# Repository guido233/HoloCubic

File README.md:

> 本 Fork 的固件已迁移到 Arduino-ESP32 3.3.12 和 LVGL 9.6，保留原版硬件接口。
> 编译、烧录、板型选择和资源迁移请阅读 [固件维护说明](2.Firmware/HoloCubic-fw/README.md)。
> 下文硬件设计与价格描述保留原作者历史记录；MPU6050 已停产，ESP32-PICO-D4 已标记为 NRND。
> Naive 硬件修订源文件在 [RevB KiCad 工程](1.Hardware/RevB-KiCad/Naive/README.md)。这是待样机验证的工程修订，采购、装配限制及检查命令均写在该目录。

# HoloCubic--多功能透明显示屏桌面站

**视频介绍：** https://www.bilibili.com/video/BV1VA411p7MD/

## 0. 关于本项目

> 稚晖君注：这是为了更新视频，缓解本人拖更两个月的尴尬，用一个周末时间赶出来的一个有意思的小玩意 :D

如视频所述，本项目有意思的地方在于使用了一个分光棱镜来设计出`伪全息显示`的效果。这个小设备总的来说功能比较多，因为搭载了WiFi和蓝牙能力可以实现很多网络应用，在本仓库中给大家提供了一个开发框架以及一些基础功能（天气、粉丝数监视器等），大家可以基于我的方案继续扩展实现更多应用。

本项目的硬件方案是基于`ESP32PICO-D4`的，乐鑫的一个很实用的MCU芯片，由于采用了SiP封装是的PCBA整板面积能做到一个硬币大小；软件方面主要是基于`lvgl-GUI`库，我移植了ST7789 1.3寸`240x240`分辨率屏幕的显示屏驱动，同时将`MPU6050`作为输入设备通过感应的方式模拟编码器键值来交互。

## 1. 硬件打样说明

原 Altium 文件保留作为历史基线。复刻前请先阅读 [Naive RevB 说明](1.Hardware/RevB-KiCad/Naive/README.md)：原板的 USB-C CC、电源、MPU6050 焊盘、上拉与背光驱动存在需要修正或验证的项目。原文的价格是历史估算，不能作为当前采购预算。

`Hardware`文件内目前包含两个版本的PCB电路：

* **Naive Version** ：即视频中出现的版本，板载ESP32、IMU、环境光传感器、SD卡槽、下载电路、以及一颗RGB灯
* **Ironman Version** ：基于上面的版本轻微修改，删去了环境光传感器，修改了PCB形状以适配新的外壳

> 因为新款的外壳计划是使用CNC进行金属加工，因此环境光容易被遮挡，而且该功能使用场景不多所以在新版删去了。

**外壳加工** 根据自己喜欢的版本选择，`3D Model`文件夹目前包含四个版本的外壳文件：

* **Naive Version** ：即视频中出现的版本，比较简约（因为临时赶工设计的），最好使用光固化3D打印加工

* **Bilibili Version** ：视频中后面出现的B站百大奖杯形式的外壳结构，适配`Naive Version`的PCB， **属于娱乐性质，非百大UP不建议采用**。

* **Metal Version** ：视频发布后全新改版的外壳结构设计，优化了布局控件整体更紧凑精致，适配`Naive Version`的PCB，该建议使用CNC加工制作

* **Ironman Version** ：新设计的野生钢铁侠风格结构件，该版本为和朋友合作设计的，后面可能会授权他联名量产，该结构适配`Ironman Version`的PCB

> 野生钢铁侠联名的版本的结构件加工比较复杂，而且需要后期喷砂、阳极氧化等工艺所以单件制造成本很高（打听了下整套3个部件至少要1000元+），因此大家自己有加工渠道的可以用提供的文件自己去做。
>
> 没有渠道但是又想要这个版本硬件的，**我授权了那位朋友量产一小批**，他的店铺名为[Xikii](https://shop68240117.taobao.com)，是做客制化键盘很有经验的一个极客，大家感兴趣的可以去关注一下~

## 2. 固件编译说明

维护版使用 PlatformIO，固定依赖版本，支持 `naive` 和 `ironman` 两种环境。Naive 为一颗 RGB 灯，Ironman 为两颗；以实际 PCB 为准。

```sh
python3 -m venv .venv
. .venv/bin/activate
python -m pip install platformio==6.1.18
pio run -d 2.Firmware/HoloCubic-fw -e naive
```

使用 Python 3.11 或更新版本。Ironman 将最后的环境名替换为 `ironman`。本版不需要复制 `Libraries`，不需要修改 ESP32 SDK 或 TFT_eSPI；屏幕和 SD 引脚由项目配置。新固件使用 4MB Flash 上的 3MiB 应用分区，首次升级应使用完整 PlatformIO 烧录流程。

完整命令、WiFi 配置、依赖版本、迁移事项和验证范围见 [固件维护说明](2.Firmware/HoloCubic-fw/README.md)。默认显示内置 Logo，提供传感器输入、SD 图片与联网查询基础功能，原视频中的所有应用仍需单独实现或移植。

## 3. 模拟器与图片转换

原 `3.Software/LvglSimulator` 的 Visual Studio 工程和 `HoloTool.exe` 保留作历史参考，使用旧版 LVGL，与当前固件的图片和接口格式不同。维护版通过主机 GUI 回归测试检查 LVGL 9 渲染与输入行为。

新版图片转换器支持 Windows、macOS 和 Linux，要求 Python 3.11 或更新版本：

```sh
python -m pip install -r 3.Software/ImageToHolo/requirements.txt
python 3.Software/ImageToHolo/get_holo.py picture.png
```

默认输出原图旁的 `picture.lv9.bin`，是 LVGL 9 RGB565 格式；复制到 SD 后用 `S:/picture.lv9.bin` 访问。原版图片需要从原图重新生成，供旧固件使用时可加 `--legacy-v7` 输出 `picture.lv7.bin`。更多选项见 `--help`。

## 4. 关于分光棱镜

我用的时25.4mm x 25.4mm x 25.4mm的棱镜，淘宝应该可以搜到，单个价格80元左右。

分光棱镜的固定比较麻烦，用胶水的话容易渗入屏幕导致水印，因此建议去TB搜一下`OCA胶`，这是一种`全贴合屏幕工艺`中用来粘合屏幕的固态胶，效果很不错也很便宜。

> 但是OCA粘性非常强，大家操作一定要仔细不要留气泡，不然粘上后就很难取下了。

## 其他的后续再补充，有用的话记得点星星~

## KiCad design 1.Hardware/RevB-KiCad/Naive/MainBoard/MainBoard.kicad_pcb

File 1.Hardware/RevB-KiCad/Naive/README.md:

# HoloCubic Naive RevB 工程修订

本目录维护 Naive 外形的原生 KiCad 10 工程。原作者的 Altium 工程保留在 `1.Hardware/Naive Version/`，没有覆盖。Ironman 尚未作本轮硬件修订。

单台整机材料见 [采购说明](PURCHASING.md)；板上用量见 [BOM.csv](BOM.csv) 和 [合并采购表](BOM-grouped.csv)。

2026-10-30 已应用首台样机的四处物料替代：主板 C24 与显示板 C4 共用 **GRM188R71E105KA12D / C86020**，每台合计 2 颗；主板 U6 改为 **TPS22918DBVT**，主板 R3 改为 **RTT022000FTH / C102869**。两板仍为 69 个位号，合并后为 38 个完整 MPN 采购行。**主板 C4 继续使用 22µF / 0805**，不属于这次 1µF 合并。替代保持原电气网络、焊盘和接口，不要求修改固件；选型已应用不代表已经实测或获得量产放行。

**当前为工程验证版本，尚未完成实物装配和通电验收。** 原生 ERC、DRC、网表一致性检查通过只能证明文件内的相应约束成立；屏幕尾排折弯、外壳净高、天线性能、USB 热插拔与供电波形仍需样机验证。不要根据文件名或一张渲染图直接批量下单。

## 打开工程

使用 KiCad 10.0 或更新的兼容版本，分别打开：

- `MainBoard/MainBoard.kicad_pro`：主板、电源、USB、ESP32、传感器、SD。
- `ExtendBoard/ExtendBoard.kicad_pro`：显示板、FFC、屏幕、背光恒流驱动。

每块板附有本地 `.pretty` 封装库、`.kicad_sym` 符号库和库表，电路与焊盘均在原生文件中，工程并非仅包含一份修改建议。macOS 从完整 KiCad 套件启动原理图编辑器；不要把内部的 `eeschema.app` 单独拷出安装，否则其相对路径共享库可能失效。

## 本轮电路修订

| 部位 | 修订内容与目的 |
| --- | --- |
| USB-C | CC1、CC2 各自接独立 5.1kΩ Rd；数据、CC 与 VBUS 增加所选器件的保护路径。USB 数据线保持两种插头方向的连接关系。 |
| 3.3V 电源 | 原 250mA LP2992 改为 TPS62162 1A 降压方案；增加电感、有效容量设计所需的输入输出电容。TPS22918 控制系统 5V 的上电斜率；RC/CT 时序需要示波器验证。 |
| USB-UART | CP2102 的 VDD6 接独立 `CP_VDD` 本地旁路，不与主板 3.3V 稳压输出并联；REGIN 增加本地去耦。 |
| MPU6050 | 删除原中心焊盘、中心锡膏与孔；中心区域禁止顶层铜、走线和过孔，遵循该封装的装配要求。 |
| ESP32-PICO | 热焊盘使用 4.5mm 接地铜、4.0mm 阻焊开口、21 个 0.25mm 热过孔，以及 16 个 0.75mm 锡膏窗口；与 MPU 的中心禁焊区分别处理。 |
| 总线与启动 | 增加 I²C 外部上拉和 SD DAT1/DAT2 上拉；保留 GPIO12 隔离；EN 电容改为 1µF；BH1750 DVI 增加复位延迟 RC。 |
| RGB | 5V WS2812B 前增加 AHCT 缓冲、旁路、串联电阻及复位默认电平，避免依赖 3.3V 直接驱动 5V 数据输入。 |
| 显示板 | 增加逻辑与 5V 本地去耦；AL5802 加 27Ω 电流设定电阻，背光典型约 24mA；NMOS 分流 EN，保持 GPIO5 低电平点亮的固件极性。 |
| FFC | 两板使用确切的 Hirose FH12-8S-0.5SH(55)，按官方 8 针焊盘替换未识别的旧封装；原文件嵌入的 16 针模型不能用于认证 8 针连接器。 |

主板仍使用 ESP32-PICO-D4、MPU6050、BH1750、CP2102 以维持复刻电路与固件接口。ESP32-PICO 系列已列为 NRND；MPU6050 已停产。它们不是当前可随意等效采购的新设计器件。采购替代、旧料来源及接口验收条件请见 [BOM 审查](BOM-review.md)。

USB1、J1、A1 已分别选定 GCT USB4105-GF-A、Molex 104031-0811、CrossAir CA-C03，采用相应厂图重新定义焊盘。Molex 完全插入后的卡端比原版左移 0.65mm，以避开 USB 贯穿固定脚；这项接口调整及下壳配合见机械审查。CA-C03 的第二端是机械焊端，保持独立未连接，不能接地。

GPIO5 是启动配置脚。显示板 Q1 选用在 2.5V 栅压下有导通规格的 AO3400A，栅极直流高阻，配合 100kΩ 上拉维持复位默认高电平；1kΩ 栅极串联电阻兼顾 5kHz 背光 PWM。此项检查需要核器件类型，单看引脚网络相同不足以确认启动电平正确。

TPS22918DBVT 与原 DBVR 是同一 DBV6 芯片的载带包装选项，ON 的硬件 RC 和 C16 定时值不变。C24 仍为 R11=1kΩ 配套的 BH1750 DVI 复位电容；显示板 C4 则是 5V 本地旁路。默认 `naive` 程序尚未接入 BH1750 读取或自动调光，本次替代不启用该功能；现存未使用的 `Ambient` helper 也需修正计时及读取错误处理后才能集成。诊断固件的光照读取不能代替 [VCC/DVI 上电复位波形验收](Closure/BRINGUP.md#bh1750-vccdvi-复位验收)。

CP2102 内部电源到 2.7V 的上升时间要求不超过 1ms（Silicon Labs 数据手册 Table 5）。TPS22918 在 CT=1nF、5V 时的输出 10–90% 上升典型值约 2.54ms，不能据此保证 CP 内部 LDO 的上升时间。因此 C16 选择 **100pF、C0G、50V、±5%（GRM1555C1H101JA01D）**，按 TI Eq.3 估算 5V 上升约 0.425ms；这是典型估算，不能代替 CP_VDD 实测。按约 13µF 有效 5V 负载电容估计，纯充电电流约 0.12–0.15A，负载启动及偏差另计。首板需同时量 CP_VDD 到 2.7V 的时间、USB 枚举和入口电流。CP2102 REGIN 的工作范围上限为 5.25V，电源应为受控 5V，不把 5.5V 当作其保证工作条件。

## 屏幕、排线与结构

P133H002 是电气接口候选：12 针、0.7mm 间距、ST7789V，VDD 与 LEDA/LEDK 分开，厂家背光电路没有内置限流。本版外置恒流驱动针对这类裸屏设计，不能把任意“1.3 寸 ST7789 模块”当作同一物料。

配套现代固件将共用 ST7789 写时钟设为 **10MHz**。现有 [Sitronix ST7789V v1.3](https://newhavendisplay.com/content/datasheets/ST7789V.pdf) 第 44 页 Table 6 要求写周期至少 66ns、高低脉宽各至少 15ns，不能据此保证先前的 40MHz。10MHz 的全帧 RGB565 纯传输时间约 92ms；更高刷新速度须先取得实际屏幕的时序保证，再在最终排线和板上测接收端建立保持时间、过冲 / 振铃，并完成并发读卡及温度 / 电源范围验证。SD 仍使用当前 Arduino 驱动默认的 4MHz，不因这一屏幕调整改动。

**P133H002 尚未通过整机机械适配验收。** 本轮把显示板改为 12 个 5.5×0.50mm 长焊盘，并重排连接器及相邻器件、完成重新布线，覆盖裸屏背折图与旧落点的纵向差异。144 项相关公差计算通过，最小纵向搭接 0.9611mm；0.75mm 是项目手工焊接阈值，不是屏厂保证。长焊盘没有 F.Paste，须在 PCBA 回流后受控手工焊接 FPC。此项只核纵向落区，不能证明尾排允许的折弯、露铜面、横向注册或整机就座；见 [显示接口计算和 1:1 图](Closure/DISPLAY-INTERFACE.md)及 [机械审查](MECHANICAL-REVIEW.md)。

两板 FFC 功能保持反序：主板 1↔显示板 8，直到主板 8↔显示板 1。已明确两端底接触及摊平后露铜同面的无交叉排线，并给出 [端部尺寸、映射和定制图要求](Closure/FFC-CABLE-SPEC.md)。最终长度仍取决于尚未锁定的整机路径；不能把 51/76mm 的有条件样品候选直接当作最终采购料号，也不能忽略其端部公差差异。

使用新的 [RevB 下壳 STEP](Mechanical/Lower-RevB.step)，与原 Naive 上壳配合。它保留外观、USB 开口和承托高度，内部增加背面元件避让槽；[实体检查记录](Mechanical/Lower-RevB-verification.json)包含来源 SHA、尺寸、体积与间隙。`tools/hardware/revb_case.py` 可重现该减材操作，依赖 `cadquery-ocp==8.0.1.1.0`。承托注册和打印公差仍需实物确认。**更换 TF 卡需要拆下壳**，本版没有新增外部取卡口。

板框与受保护孔位由 `tools/hardware/baseline.json` 记录，保留原 Altium 文件 SHA。原两层设计有约 1.000mm 介质和两面约 35.56µm 铜，总厚约 1.071mm（不含阻焊），这是历史几何基准，不能作为本轮主板的最终制造厚度。

本轮主板采用**六层原型方案**，最终布线与检查记录以本目录冻结的工程为准：F.Cu / In1.Cu / In2.Cu / In3.Cu / In4.Cu / B.Cu。In1、In4 为专用 GND 层；In2 混合承载 3V3 铜面、其它电源与信号；In3 承载信号与 GND 铜面。显示板保留两层。三处严格 RF 内层禁布区覆盖四个内层，原七段外层 RF 几何保持；这一约束不等于天线匹配或阻抗已经验证，仍需在实际层叠与外壳内做 VNA 和无线性能测试。

当前选择 JLCPCB 公开的 **JLC06101H-3313** 六层、订单名义 1.0mm 模板。公开铜与介质合计 1.04mm，加当前双面阻焊预算后 CAD 总厚 **1.06mm**。这已替换先前自定义的 1.0192mm 层叠；[完整公开请求/响应、模板参数和 DFM 约定](Closure/STACKUP-SPEC.md)均已保存。工程选择不等于板厂已经接受本工程订单，交付总厚口径及公差仍须回签。

| 自顶向下 | CAD 名义厚度 |
| --- | ---: |
| F.Mask / F.Cu | 10µm / 35µm |
| prepreg / In1.Cu | 99.4µm / 15.2µm |
| core / In2.Cu | 250µm / 15.2µm |
| prepreg / In3.Cu | 210.4µm / 15.2µm |
| core / In4.Cu | 250µm / 15.2µm |
| prepreg / B.Cu / B.Mask | 99.4µm / 35µm / 10µm |

模板的 3313/core/7628 厚度及公开设计 Dk 已同步 PCB，移除无依据的 Df 占位值；不宣称控阻抗或 RF 已合格。已按 1.06mm 重新筛查主板与壳体、USB 的几何关系。订单名义 1.0mm、模板铜与介质 1.04mm、CAD 含阻焊预算 1.06mm 不是同一厚度定义，须取得板厂交付口径和范围。受保护孔位及接口修订使用显式 profile，不改写历史 Altium 基线。

主板属于密集双面贴装。制造商须确认约 0.102mm 局部细线、0.127mm 铜间距、0.25mm 成品孔及至少 0.10mm 孔环的能力；电源主干使用更宽走线。GCT 自身孔与焊盘的厂图间距约 0.194mm，由限定在 USB1 内部的 0.19mm 规则检查，板上其余孔仍要求 0.20mm。两板收紧为阻焊桥至少 0.10mm、开窗到异网铜至少 0.09mm；显示板外扩调整为 +0.025mm 后原 33 项阻焊错误归零。询价目标采用绿色阻焊、ENIG，PICO 热孔单独标识树脂填孔盖镀并保留底面阻焊，80µm 钢网作为装配评估起点；不得把盖油等同填孔，最终工艺由制造方回签。

## 检查

2026-10-29 基准及 2026-10-30 物料替代应用的实际检查结果，以 [检查记录](VALIDATION.md) 和 [可追溯结果](validation-results.json) 中相应的源文件 SHA 为准。

在仓库根目录执行；`kicad-cli` 可以在 PATH，也可通过 `--cli` 给出绝对路径：

```sh
python3 tools/hardware/verify_hardware.py --drc --output /tmp/holocubic-checks.json
python3 -m unittest discover -s tools/hardware -p 'test_*.py' -v
```

验证器重新导出原生网表、运行 ERC/DRC，并核对两板所有引脚节点集合、网络名、料值、封装、原理图 UUID 链接，以及电源隔离、CC、电平缓冲、SD/I²C 上拉、背光路径、MPU 禁布区和 PICO 热焊盘。故障注入测试检查验证器能识别错误连接、启动脚加载及不当锡膏等故障。报告记录原生工具的规则、忽略项和失败项；检查脚本不会修改工程或把实测结果写成通过。

`revise_mainboard.py`、`revise_extendboard.py` 是从原始导入建立本轮布局的工程迁移工具，**重新运行会产生需要重新布线的布局**。日常维护请直接编辑本目录原生工程，修改后重新运行验证，不要把布局生成成功当成完成布线。

## 首块样机的释放条件

本轮已完成的文件修订、仍待厂家资料或实物验证的项目见 [闭合状态](Closure/README.md)。新增 [诊断固件、测量位置和记录表](Closure/BRINGUP.md)只准备验收工具，尚未在样机上执行。

先锁定所有关键料号和推荐焊盘，完成屏幕/FFC/壳体的实物配合，再检查短路、限流上电、5V 与 3.3V 启动/负载阶跃、USB-C 两个方向和热插拔、串口枚举/自动下载、背光实际电流与温升、SD 读写和 WiFi 同时运行、传感器及天线在最终外壳内的表现。背光 24mA 来自典型 VBE/27Ω，不能用 1% 电阻公差推导成全温恒定电流保证；需实际测量。

电源预算要求合格 5V 电源及线缆，建议额定至少 1A。满负载不能假定所有电脑 USB 2.0 的 500mA 端口都足够；CC Rd 也不是 USB PD 或电流档位检测器。本工程没有完成 USB 合规认证。

## 主要原厂依据

- [TI TPS62162 数据手册](https://www.ti.com/lit/ds/symlink/tps62162.pdf)、[TPS22918 数据手册](https://www.ti.com/lit/ds/symlink/tps22918.pdf)：电源及上电控制。
- [Silicon Labs CP2102/9 数据手册](https://www.silabs.com/documents/public/data-sheets/CP2102-9.pdf)：VDD/REGIN、典型应用与输入额定；不能套用 CP2102N 的不同要求。
- [Diodes AL5802 数据手册](https://www.diodes.com/datasheet/download/AL5802.pdf)：低边电流设定和外部 NMOS 分流 EN 的调光方式。
- [POLCD P133H002](https://www.polcd-digital.com/products/1-3-inch-tft-lcd-display-240x240-pixels-p133h002)：候选屏接口、背光和机械尺寸。
- [Hirose FH12-8S-0.5SH(55)](https://www.hirose.com/en/product/p/CL0586-0744-5-55)：8 针、底接触、0.3mm FFC/FPC、2mm 高连接器。
- [Espressif ESP32-PICO 系列数据手册](https://documentation.espressif.com/esp32-pico_series_datasheet_en.html)：针脚、电源与 NRND 状态。

这些文件保留原项目的著作权和许可证；RevB 新增内容的维护记录在 Git 提交中。

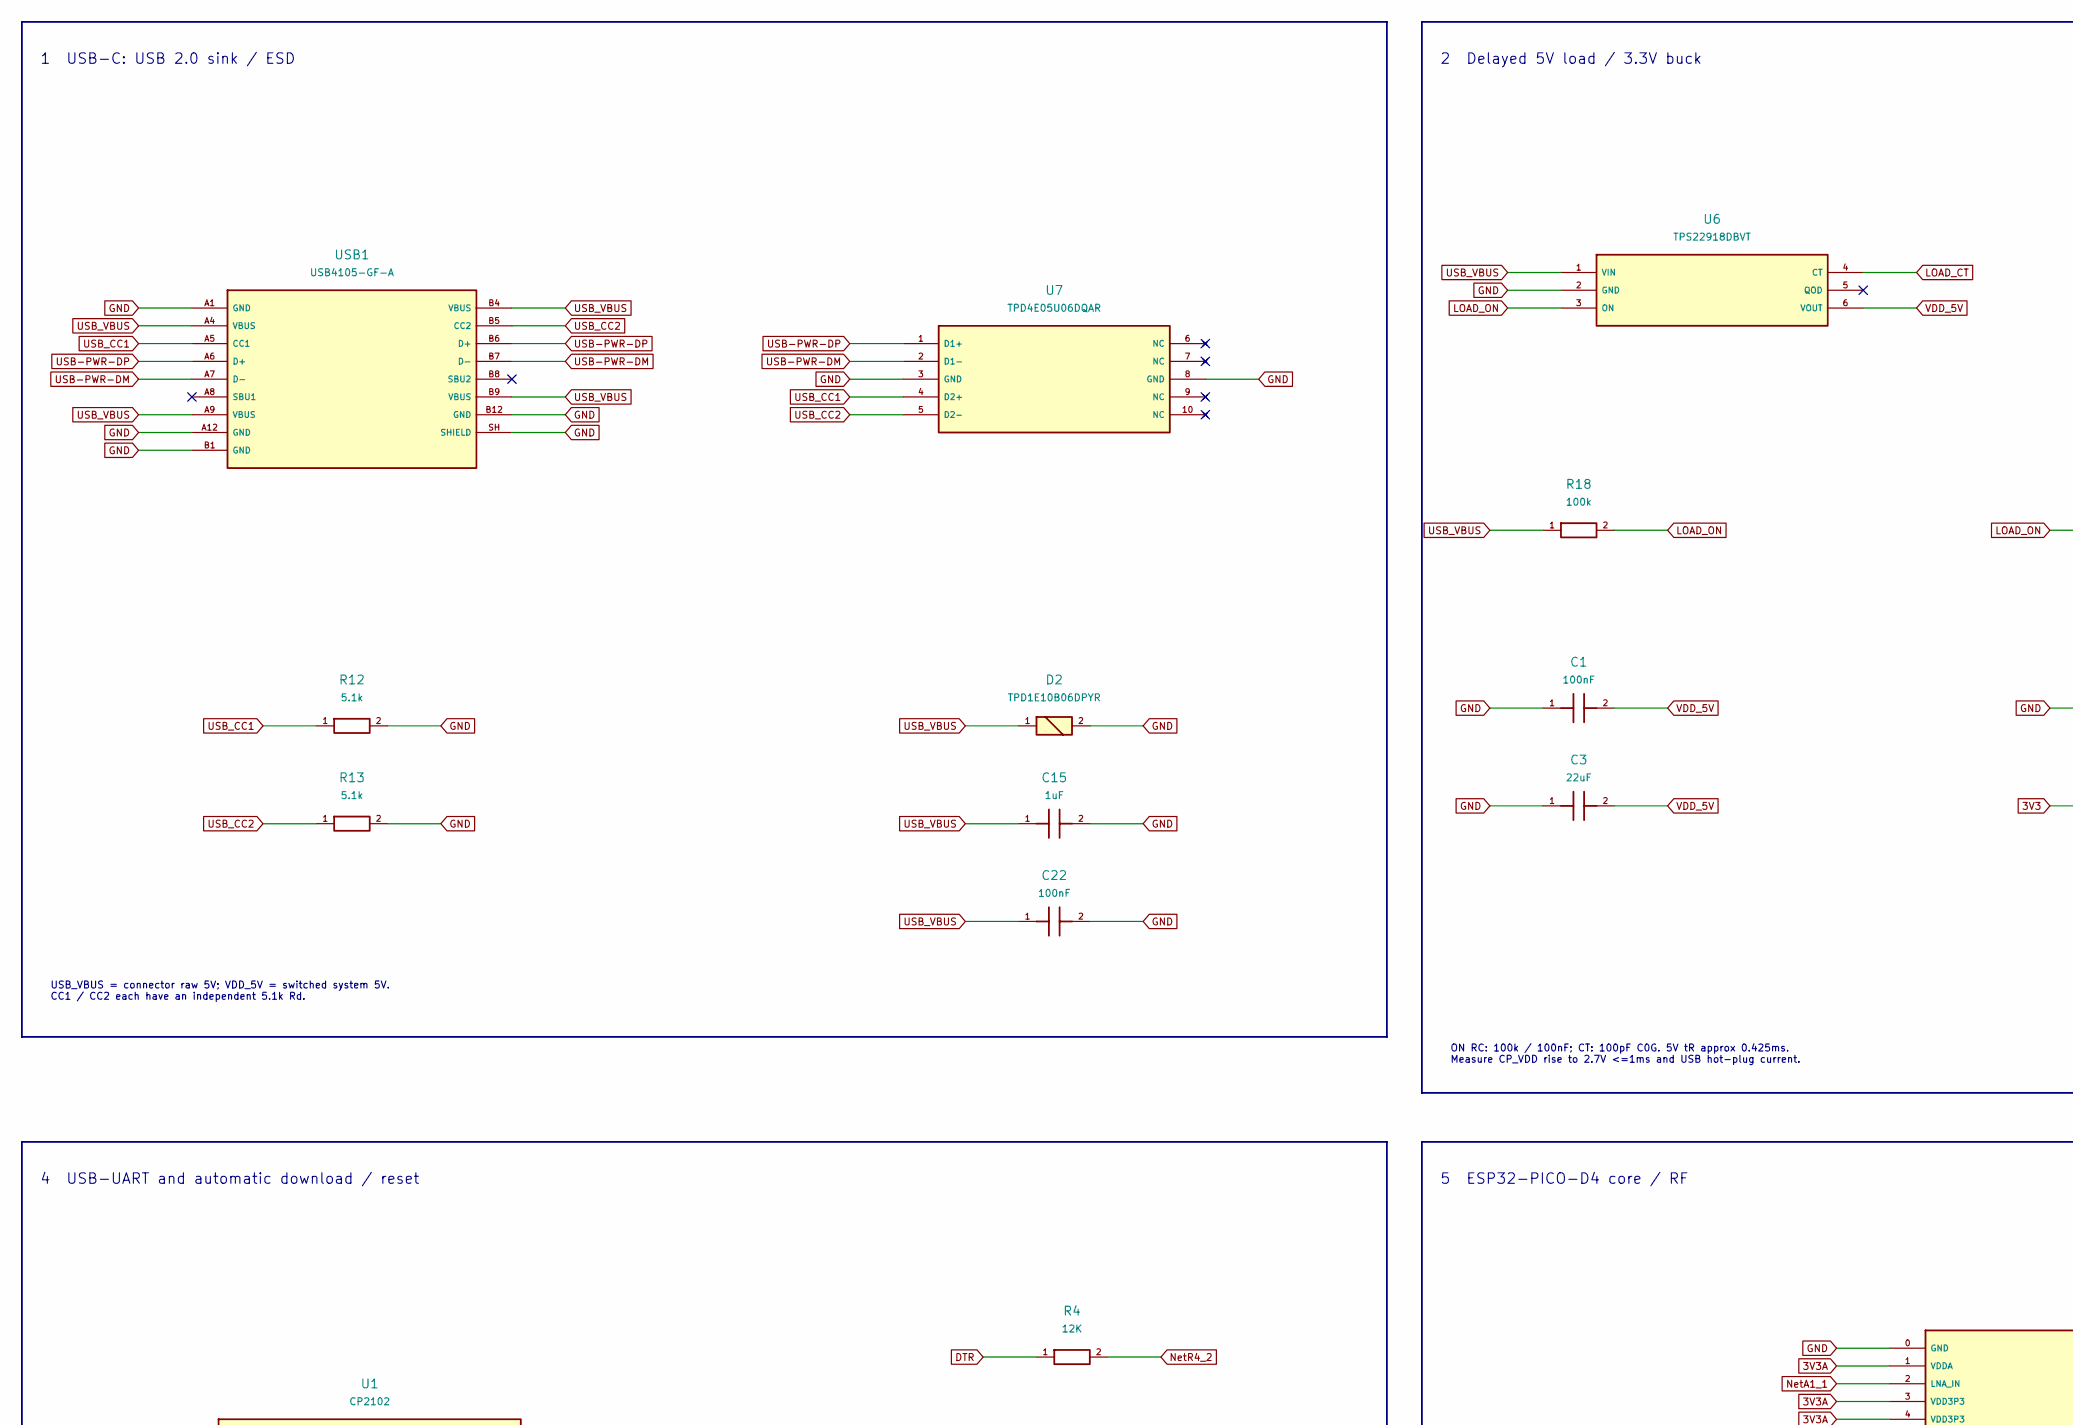
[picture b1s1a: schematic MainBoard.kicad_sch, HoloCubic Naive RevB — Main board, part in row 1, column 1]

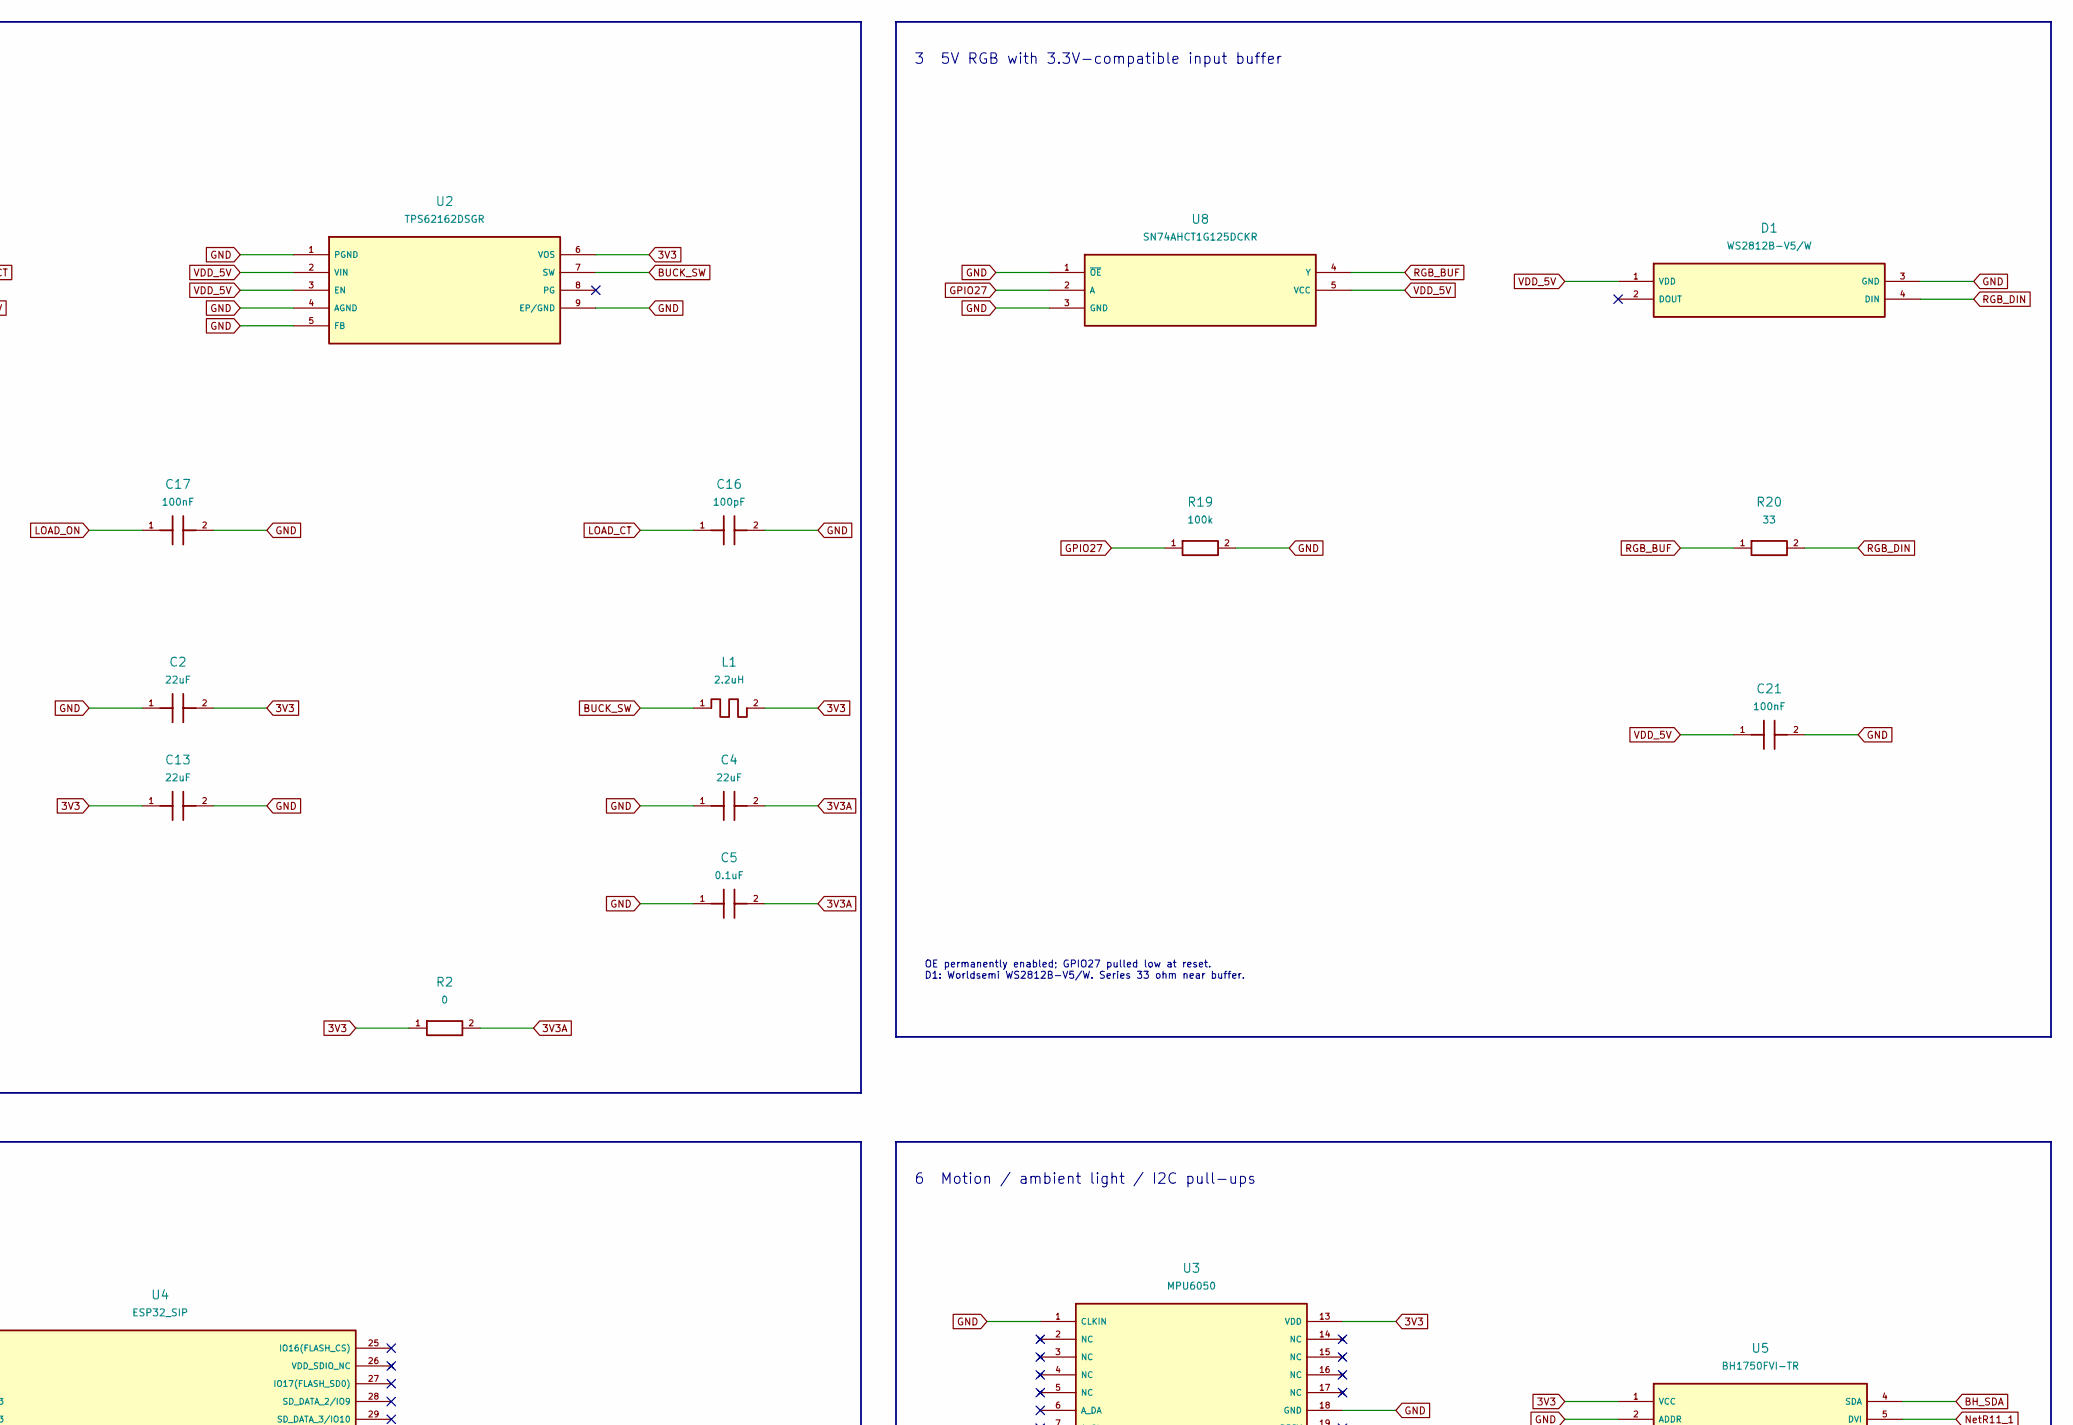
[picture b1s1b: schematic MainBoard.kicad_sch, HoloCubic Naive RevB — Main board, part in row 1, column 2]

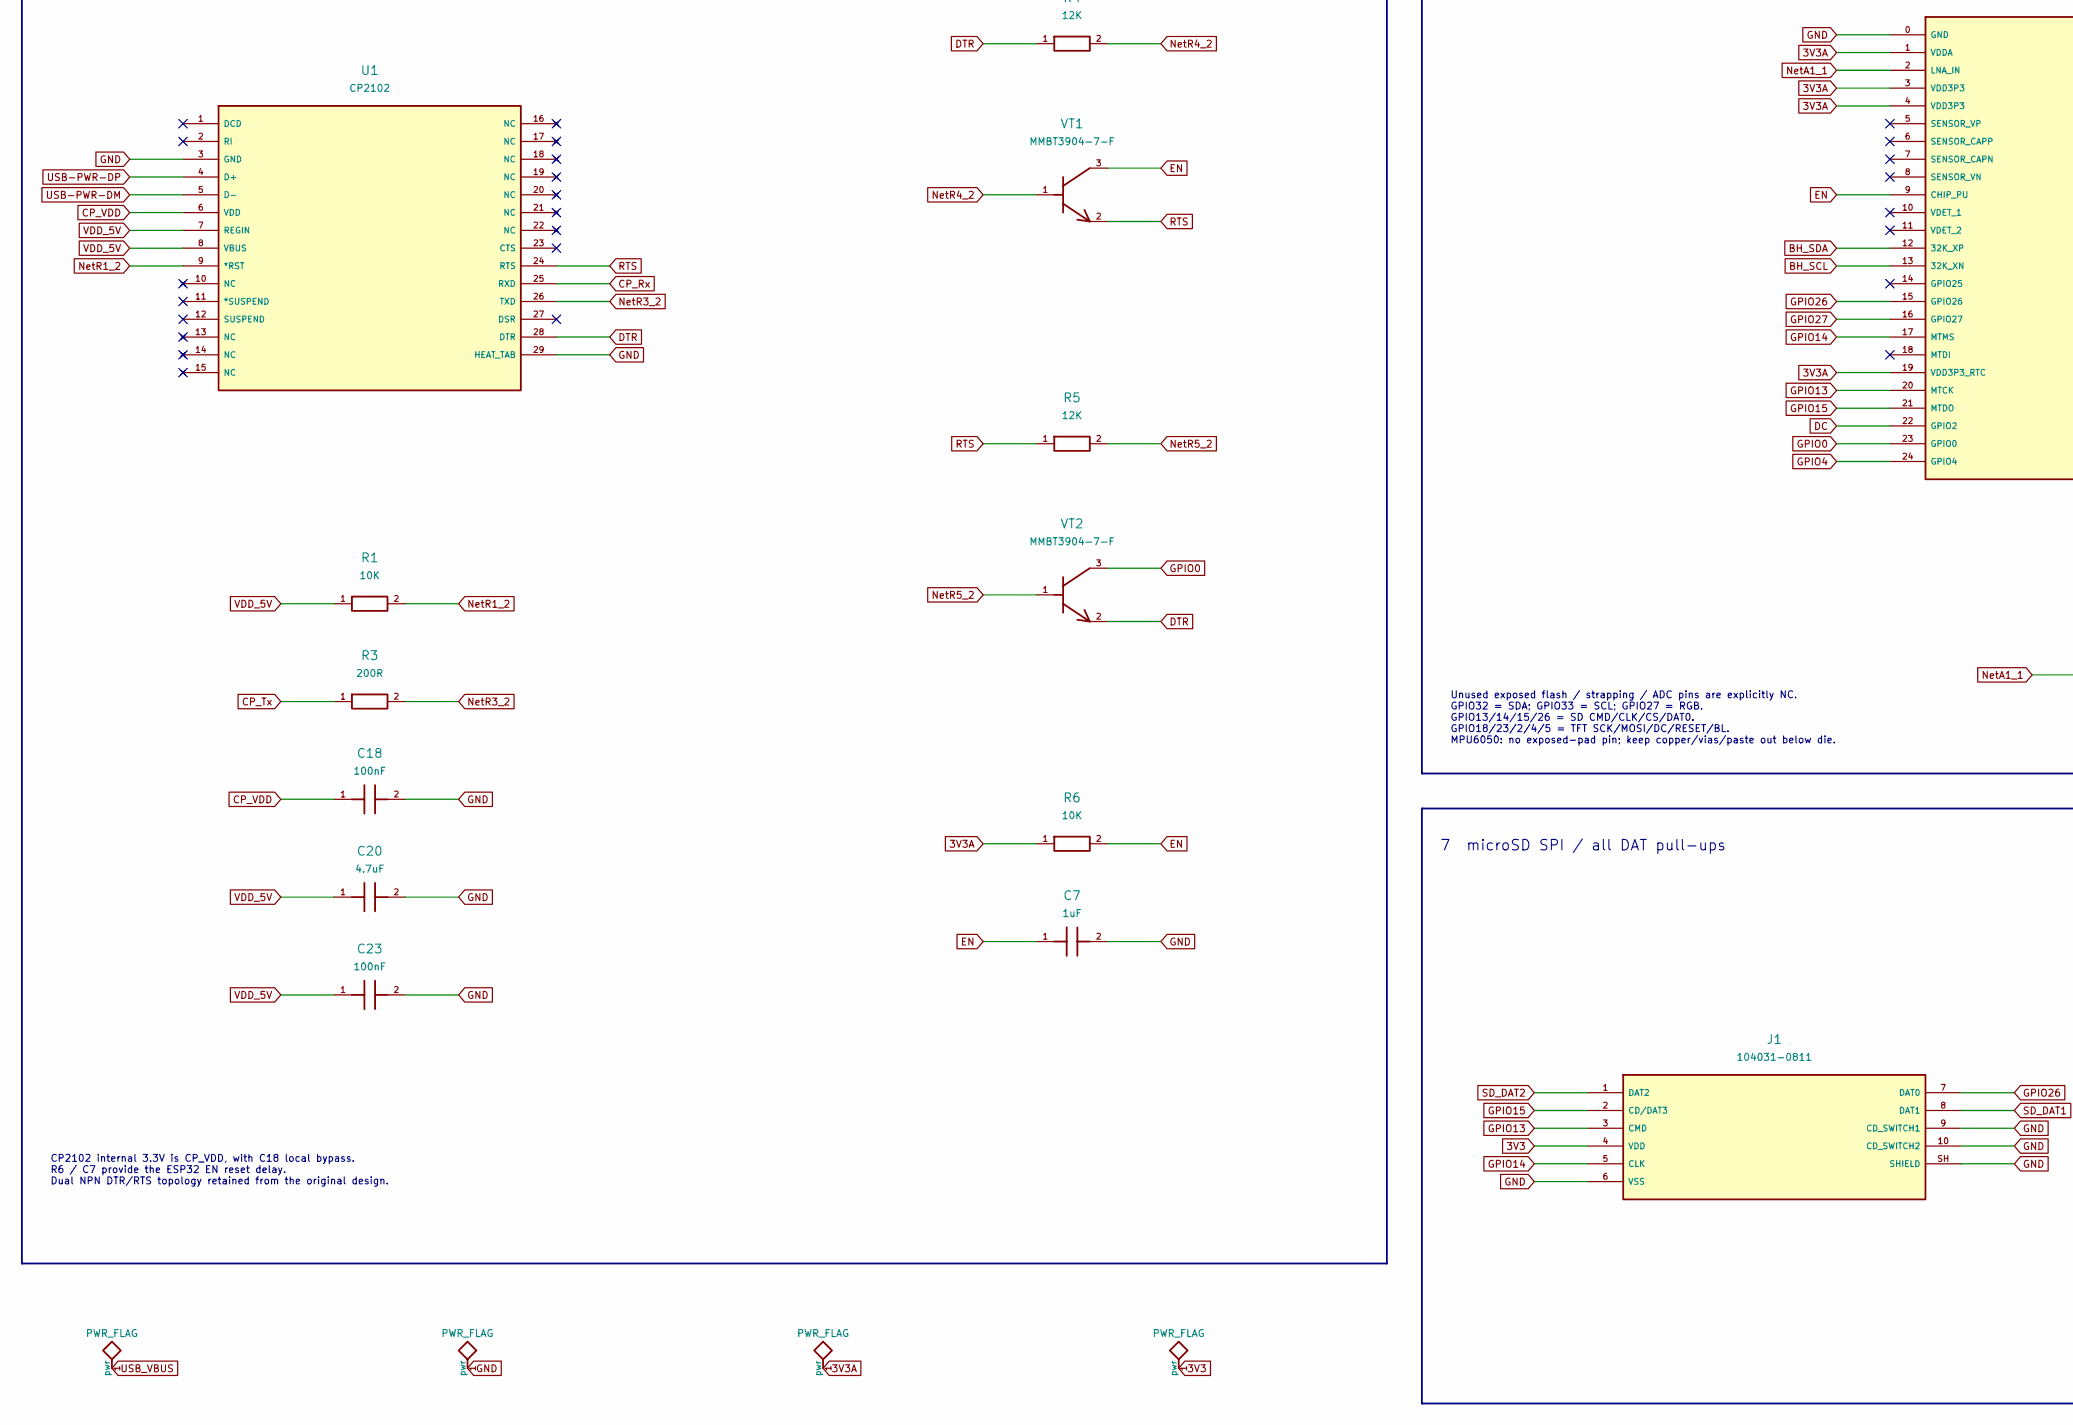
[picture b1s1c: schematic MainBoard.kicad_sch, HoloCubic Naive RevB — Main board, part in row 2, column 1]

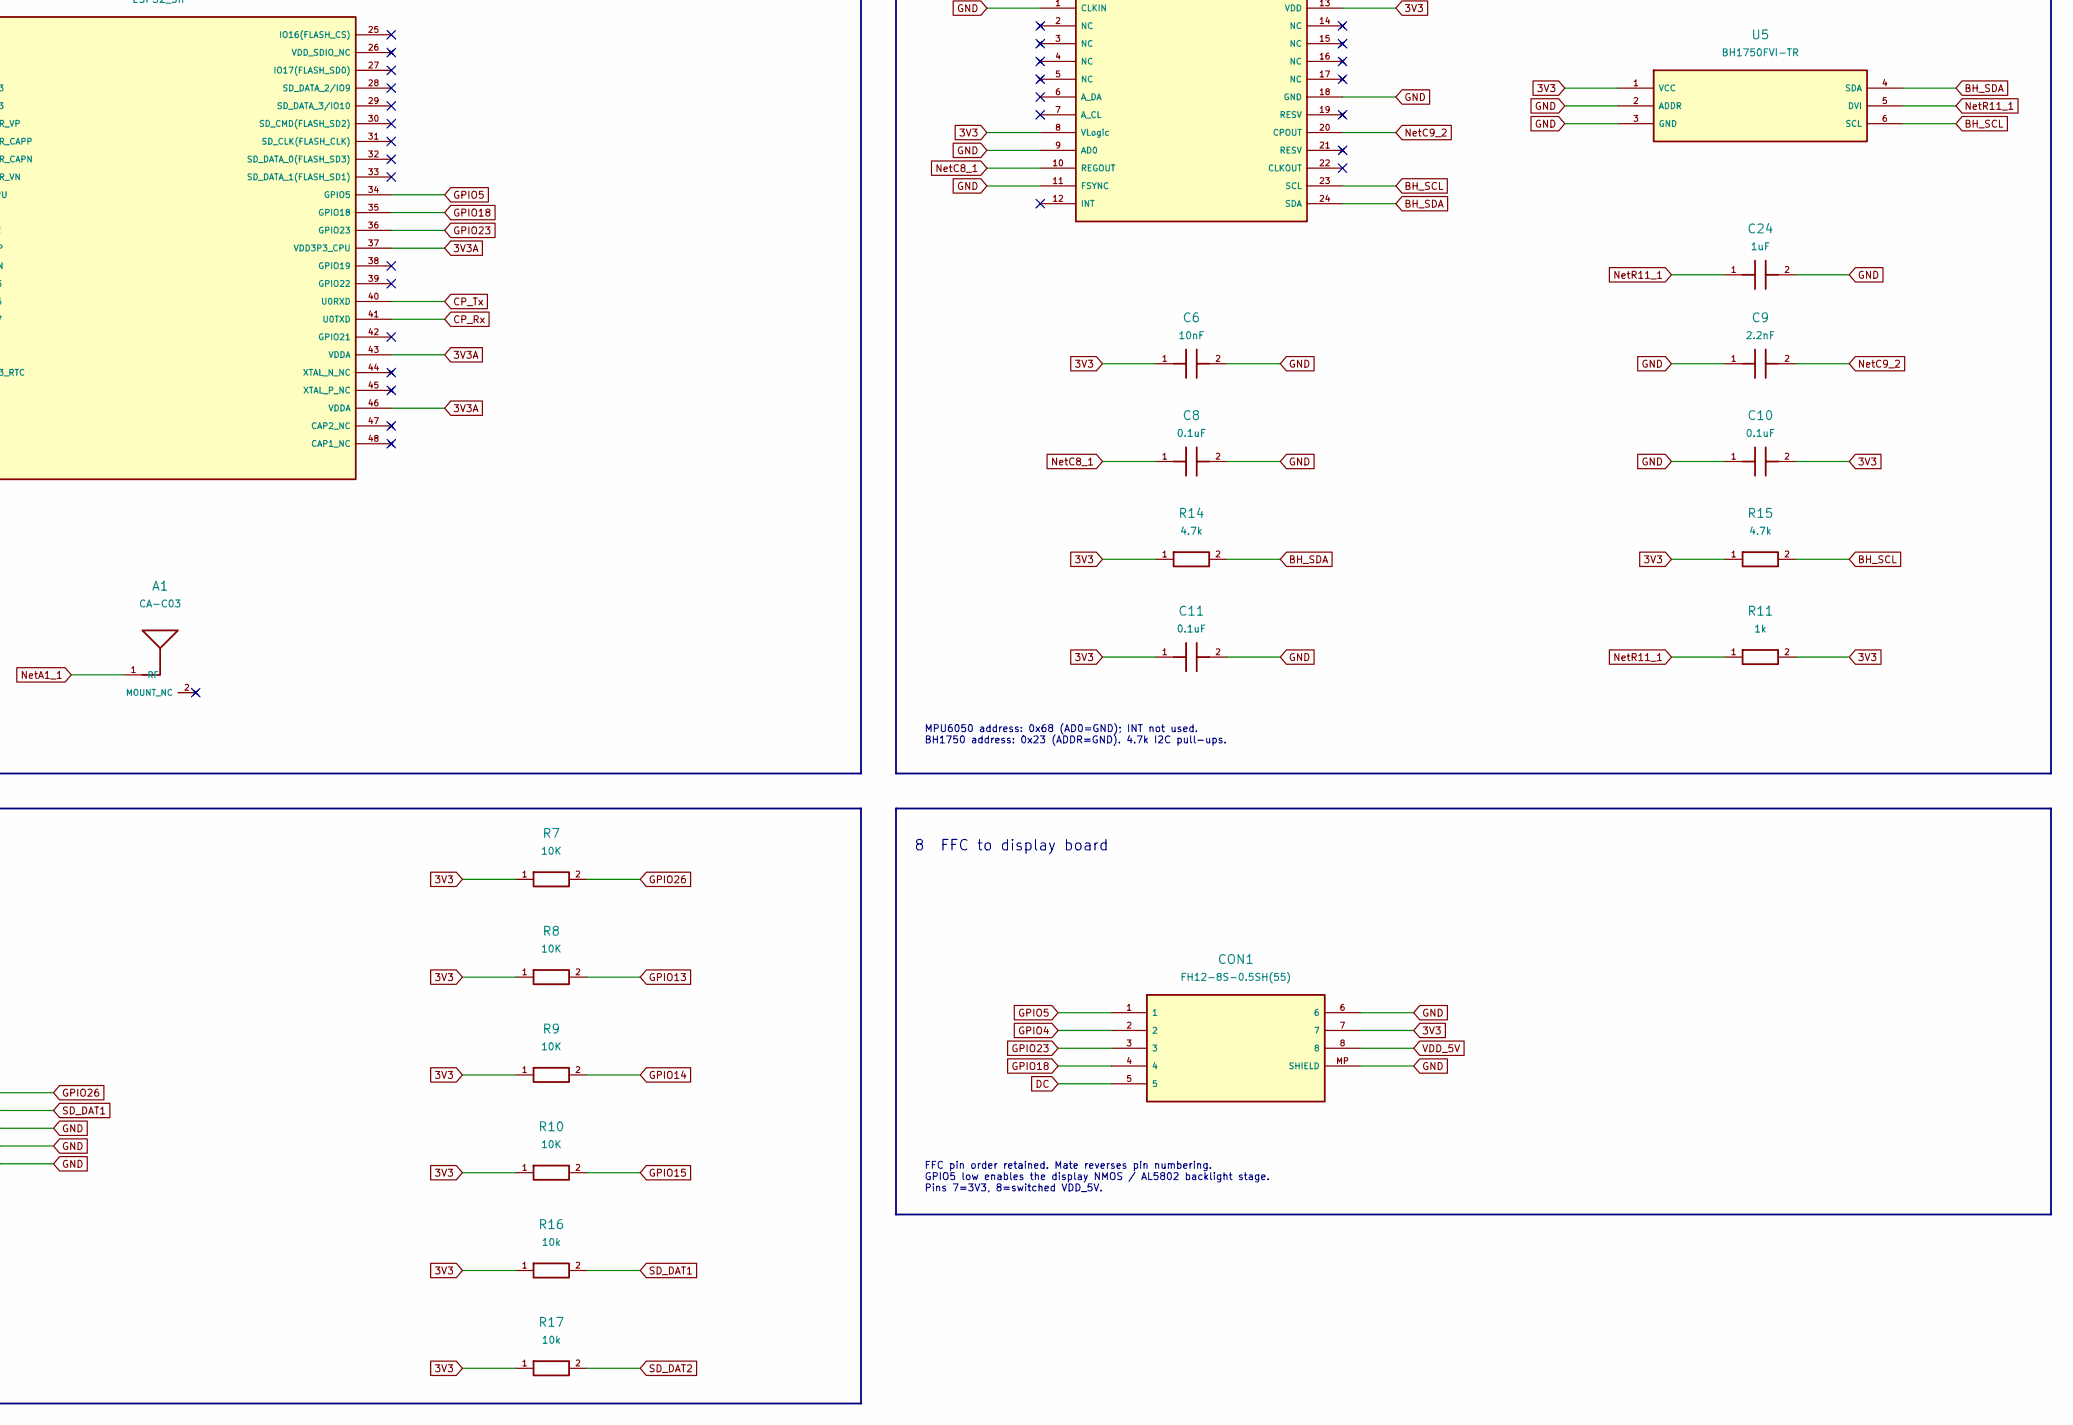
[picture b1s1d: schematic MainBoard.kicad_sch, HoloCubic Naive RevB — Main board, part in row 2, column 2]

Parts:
A1: CA-C03; RevB_A1; MPN CA-C03
C1: 100nF; RevB_C1; MPN GRM155R71C104KA88D
C2: 22uF; RevB_C2; MPN GRM21BR61E226ME44L
C3: 22uF; RevB_C3; MPN GRM21BR61E226ME44L
C4: 22uF; RevB_C4; MPN GRM21BR61E226ME44L
C5: 0.1uF; Original_C5; MPN GRM155R71C104KA88D
C6: 10nF; Original_C6; MPN GRM155R71H103KA88D
C7: 1uF; RevB_C7; MPN GRM155R61C105KA12D
C8: 0.1uF; Original_C8; MPN GRM155R71C104KA88D
C9: 2.2nF; Original_C9; MPN GRM1555C1H222JA01D
C10: 0.1uF; Original_C10; MPN GRM155R71C104KA88D
C11: 0.1uF; Original_C11; MPN GRM155R71C104KA88D
C13: 22uF; RevB_C13; MPN GRM21BR61E226ME44L
C15: 1uF; RevB_C15; MPN GRM155R61C105KA12D
C16: 100pF; RevB_C16; MPN GRM1555C1H101JA01D
C17: 100nF; RevB_C17; MPN GRM155R71C104KA88D
C18: 100nF; RevB_C18; MPN GRM155R71C104KA88D
C20: 4.7uF; RevB_C20; MPN GRM155R61A475MEAAD
C21: 100nF; RevB_C21; MPN GRM155R71C104KA88D
C22: 100nF; RevB_C22; MPN GRM155R71C104KA88D
C23: 100nF; RevB_C23; MPN GRM155R71C104KA88D
C24: 1uF; RevB_C24; MPN GRM188R71E105KA12D
CON1: FH12-8S-0.5SH(55); RevB_CON1; MPN FH12-8S-0.5SH(55)
D1: WS2812B-V5/W; Original_D1; MPN WS2812B-V5/W
D2: TPD1E10B06DPYR; RevB_D2; MPN TPD1E10B06DPYR
J1: 104031-0811; RevB_J1; MPN 104031-0811
L1: 2.2uH; RevB_L1; MPN VLS3012HBX-2R2M-N
R1: 10K; Original_R1; MPN RC0402FR-0710KL
R2: 0; RevB_R2; MPN RC0402JR-070RL
R3: 200R; Original_R3; MPN RTT022000FTH
R4: 12K; Original_R4; MPN RC0402FR-0712KL
R5: 12K; Original_R5; MPN RC0402FR-0712KL
R6: 10K; Original_R6; MPN RC0402FR-0710KL
R7: 10K; Original_R7; MPN RC0402FR-0710KL
R8: 10K; Original_R8; MPN RC0402FR-0710KL
R9: 10K; Original_R9; MPN RC0402FR-0710KL
R10: 10K; Original_R10; MPN RC0402FR-0710KL
R11: 1k; RevB_R11; MPN RC0402FR-071KL
R12: 5.1k; RevB_R12; MPN RC0402FR-075K1L
R13: 5.1k; RevB_R13; MPN RC0402FR-075K1L
R14: 4.7k; RevB_R14; MPN RC0402FR-074K7L
R15: 4.7k; RevB_R15; MPN RC0402FR-074K7L
R16: 10k; RevB_R16; MPN RC0402FR-0710KL
R17: 10k; RevB_R17; MPN RC0402FR-0710KL
R18: 100k; RevB_R18; MPN RC0402FR-07100KL
R19: 100k; RevB_R19; MPN RC0402FR-07100KL
R20: 33; RevB_R20; MPN RC0402FR-0733RL
U1: CP2102; Original_U1; MPN CP2102-GMR
U2: TPS62162DSGR; RevB_U2; MPN TPS62162DSGR
U3: MPU6050; Original_U3; MPN MPU-6050
U4: ESP32_SIP; RevB_U4; MPN ESP32-PICO-D4
U5: BH1750FVI-TR; Original_U5; MPN BH1750FVI-TR
U6: TPS22918DBVT; RevB_U6; MPN TPS22918DBVT
U7: TPD4E05U06DQAR; RevB_U7; MPN TPD4E05U06DQAR
U8: SN74AHCT1G125DCKR; RevB_U8; MPN SN74AHCT1G125DCKR
USB1: USB4105-GF-A; RevB_USB1; MPN USB4105-GF-A
VT1: MMBT3904-7-F; RevB_VT1; MPN MMBT3904-7-F
VT2: MMBT3904-7-F; RevB_VT2; MPN MMBT3904-7-F

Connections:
3V3: C2.2, C6.1, C10.2, C11.1, C13.1, CON1.7, J1.4 (VDD), L1.2, R2.1, R7.1, R8.1, R9.1, R10.1, R11.2, R14.1, R15.1, R16.1, R17.1, U2.6 (VOS), U3.8 (VLogic), U3.13 (VDD), U5.1 (VCC)
3V3A: C4.2, C5.2, R2.2, R6.1, U4.1 (VDDA), U4.3 (VDD3P3), U4.4 (VDD3P3), U4.19 (VDD3P3_RTC), U4.37 (VDD3P3_CPU), U4.43 (VDDA), U4.46 (VDDA)
BH_SCL: R15.2, U3.23 (SCL), U4.13 (32K_XN), U5.6 (SCL)
BH_SDA: R14.2, U3.24 (SDA), U4.12 (32K_XP), U5.4 (SDA)
BUCK_SW: L1.1, U2.7 (SW)
CP_Rx: U1.25 (RXD), U4.41 (U0TXD)
CP_Tx: R3.1, U4.40 (U0RXD)
CP_VDD: C18.1, U1.6 (VDD)
DC: CON1.5, U4.22 (GPIO2)
DTR: R4.1, U1.28 (DTR), VT2.2
EN: C7.1, R6.2, U4.9 (CHIP_PU), VT1.3
GND: C1.1, C2.1, C3.1, C4.1, C5.1, C6.2, C7.2, C8.2, C9.1, C10.1, C11.2, C13.2, C15.2, C16.2, C17.2, C18.2, C20.2, C21.2, C22.2, C23.2, C24.2, CON1.6, CON1.MP (SHIELD), D1.3 (GND), D2.2, J1.6 (VSS), J1.9 (CD_SWITCH1), J1.10 (CD_SWITCH2), J1.SH (SHIELD), R12.2, R13.2, R19.2, U1.3 (GND), U1.29 (HEAT_TAB), U2.1 (PGND), U2.4 (AGND), U2.5 (FB), U2.9 (EP/GND), U3.1 (CLKIN), U3.9 (AD0), U3.11 (FSYNC), U3.18 (GND), U4.0 (GND), U5.2 (ADDR), U5.3 (GND), U6.2 (GND), U7.3 (GND), U7.8 (GND), U8.1 (~OE), U8.3 (GND), USB1.A1 (GND), USB1.A12 (GND), USB1.B1 (GND), USB1.B12 (GND), USB1.SH (SHIELD)
GPIO0: U4.23 (GPIO0), VT2.3
GPIO4: CON1.2, U4.24 (GPIO4)
GPIO5: CON1.1, U4.34 (GPIO5)
GPIO13: J1.3 (CMD), R8.2, U4.20 (MTCK)
GPIO14: J1.5 (CLK), R9.2, U4.17 (MTMS)
GPIO15: J1.2 (CD/DAT3), R10.2, U4.21 (MTDO)
GPIO18: CON1.4, U4.35 (GPIO18)
GPIO23: CON1.3, U4.36 (GPIO23)
GPIO26: J1.7 (DAT0), R7.2, U4.15 (GPIO26)
GPIO27: R19.1, U4.16 (GPIO27), U8.2 (A)
LOAD_CT: C16.1, U6.4 (CT)
LOAD_ON: C17.1, R18.2, U6.3 (ON)
NetA1_1: A1.1 (RF), U4.2 (LNA_IN)
NetC8_1: C8.1, U3.10 (REGOUT)
NetC9_2: C9.2, U3.20 (CPOUT)
NetR1_2: R1.2, U1.9 (*RST)
NetR3_2: R3.2, U1.26 (TXD)
NetR4_2: R4.2, VT1.1
NetR5_2: R5.2, VT2.1
NetR11_1: C24.1, R11.1, U5.5 (DVI)
RGB_BUF: R20.1, U8.4 (Y)
RGB_DIN: D1.4 (DIN), R20.2
RTS: R5.1, U1.24 (RTS), VT1.2
SD_DAT1: J1.8 (DAT1), R16.2
SD_DAT2: J1.1 (DAT2), R17.2
USB-PWR-DM: U1.5 (D-), U7.2 (D1-), USB1.A7 (D-), USB1.B7 (D-)
USB-PWR-DP: U1.4 (D+), U7.1 (D1+), USB1.A6 (D+), USB1.B6 (D+)
USB_CC1: R12.1, U7.4 (D2+), USB1.A5 (CC1)
USB_CC2: R13.1, U7.5 (D2-), USB1.B5 (CC2)
USB_VBUS: C15.1, C22.1, D2.1, R18.1, U6.1 (VIN), USB1.A4 (VBUS), USB1.A9 (VBUS), USB1.B4 (VBUS), USB1.B9 (VBUS)
VDD_5V: C1.2, C3.2, C20.1, C21.1, C23.1, CON1.8, D1.1 (VDD), R1.1, U1.7 (REGIN), U1.8 (VBUS), U2.2 (VIN), U2.3 (EN), U6.6 (VOUT), U8.5 (VCC)

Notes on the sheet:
1 USB-C: USB 2.0 sink / ESD
2 Delayed 5V load / 3.3V buck
3 5V RGB with 3.3V-compatible input buffer
4 USB-UART and automatic download / reset
5 ESP32-PICO-D4 core / RF
6 Motion / ambient light / I2C pull-ups
7 microSD SPI / all DAT pull-ups
8 FFC to display board
USB_VBUS = connector raw 5V; VDD_5V = switched system 5V. CC1 / CC2 each have an independent 5.1k Rd.
ON RC: 100k / 100nF; CT: 100pF C0G. 5V tR approx 0.425ms. Measure CP_VDD rise to 2.7V <=1ms and USB hot-plug current.
OE permanently enabled; GPIO27 pulled low at reset. D1: Worldsemi WS2812B-V5/W. Series 33 ohm near buffer.
CP2102 internal 3.3V is CP_VDD, with C18 local bypass. R6 / C7 provide the ESP32 EN reset delay. Dual NPN DTR/RTS topology retained from the original design.
Unused exposed flash / strapping / ADC pins are explicitly NC. GPIO32 = SDA; GPIO33 = SCL; GPIO27 = RGB. GPIO13/14/15/26 = SD CMD/CLK/CS/DAT0. GPIO18/23/2/4/5 = TFT SCK/MOSI/DC/RESET/BL. MPU6050: no exposed-pad pin; keep copper/vias/paste out below die.
MPU6050 address: 0x68 (AD0=GND); INT not used. BH1750 address: 0x23 (ADDR=GND). 4.7k I2C pull-ups.
FFC pin order retained. Mate reverses pin numbering. GPIO5 low enables the display NMOS / AL5802 backlight stage. Pins 7=3V3, 8=switched VDD_5V.

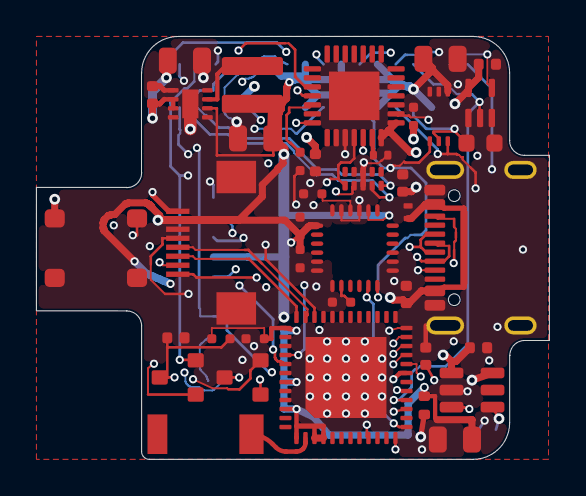
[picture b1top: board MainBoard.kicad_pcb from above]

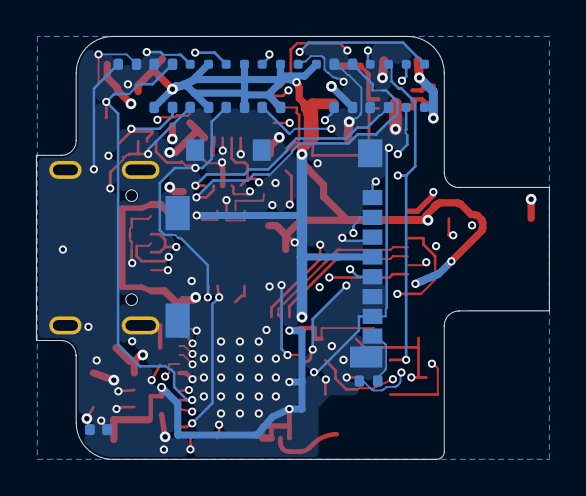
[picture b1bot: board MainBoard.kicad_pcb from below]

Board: 6 copper layers, 28.5 x 23.5 mm, 58 parts (19 on the bottom side), 43 nets.

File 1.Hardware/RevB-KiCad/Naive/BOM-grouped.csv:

MPN,Value,Quantity,Manufacturer,Board:Reference,Supply status,Acceptance notes,Source
104031-0811,104031-0811,1,Molex,MainBoard:J1,Active（原厂）,RevB2焊盘；检测9/10均GND未用；需插卡及保卡实测,https://www.molex.com/en-us/products/part-detail/1040310811
AL5802-7,AL5802,1,Diodes Incorporated,ExtendBoard:U1,未单独核验生命周期,SOT26恒流驱动；27ohm设约24mA典型值，须测实物背光电流,https://www.diodes.com/assets/Datasheets/AL5802.pdf
AO3400A,AO3400A,1,Alpha & Omega Semiconductor,ExtendBoard:Q1,未单独核验生命周期,G1/S2/D3逻辑NMOS；不可用NPN替代，以免加载GPIO5启动strap,https://www.aosmd.com/sites/default/files/res/datasheets/AO3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
BH1750FVI-TR,BH1750FVI-TR,1,ROHM,MainBoard:U5,NRND（渠道，待原厂确认）,WSOF6I；向原厂/授权渠道确认供货与追溯，不以模块代替裸IC,https://mm.digikey.com/Volume0/opasdata/d220001/medias/docus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
CA-C03,CA-C03,1,CrossAir / 广州寒武纪,MainBoard:A1,厂家资料已核,工程焊盘偏离厂家推荐尺寸；pin2固定端NC；需焊接、VNA及整壳RF验收,https://www.gzhwjdz.com/DownLoad/45858.html
CP2102-GMR,CP2102,1,Silicon Labs,MainBoard:U1,预计完整生产至少至2029-03,经典CP2102 QFN28；核优选修订与可追溯批次，不以CP2102N替代,https://www.silabs.com/interface/usb-bridges/classic/device.cp2102
ESP32-PICO-D4,ESP32_SIP,1,Espressif,MainBoard:U4,NRND（原厂）,PICO系列v1.5均NRND；保持D4，替代需重新设计；EP/paste/via按RevB受控封装,https://documentation.espressif.com/esp32-pico_series_datash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
FH12-8S-0.5SH(55),FH12-8S-0.5SH(55),2,Hirose,"MainBoard:CON1, ExtendBoard:CON1",厂家图纸已核,8P / 0.5mm / 0.3mm厚FFC，bottom contact；排线接触面及长度另行锁定,https://www.hirose.com/product/p/CL0586-0744-5-55
GRM1555C1H101JA01D,100pF,1,Murata,MainBoard:C16,原理图已选完整MPN,100pF/50V/C0G±5%0402；TI Eq3估算约0.425ms@5V，非最大值保证；CP_VDD到2.7V≤1ms、热插拔与入口电流须实测,https://ds.murata.com/simserve/characteristics?ReqType=TechP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
GRM1555C1H222JA01D,2.2nF,1,Murata,MainBoard:C9,原理图已选完整MPN,MLCC标称值不代表工作偏压下有效值,https://ds.murata.com/simserve/characteristics?ReqType=TechP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
GRM155R61A475MEAAD,4.7uF,1,Murata,MainBoard:C20,原理图已选完整MPN,4.7uF/10V/X5R0402；5V典型约1.88uF、5.5V约1.7uF；非保证下限，量产须采样,https://ds.murata.com/simserve/characteristics?ReqType=TechP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
GRM155R61C105KA12D,1uF,2,Murata,"MainBoard:C7, MainBoard:C15",原理图已选完整MPN,1uF/16V0402；3V3典型有效约0.55uF，EN实际复位时序须测; 入口1uF/16V0402；5V典型有效约0.35uF；热插拔时序须测,https://ds.murata.com/simserve/characteristics?ReqType=TechP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
GRM155R71C104KA88D,100nF / 0.1uF,12,Murata,"MainBoard:C1, MainBoard:C5, MainBoard:C8, MainBoard:C10, MainBoard:C11, MainBoard:C17, MainBoard:C18, MainBoard:C21, MainBoard:C22, MainBoard:C23, ExtendBoard:C1, ExtendBoard:C3",原理图已选完整MPN,MLCC标称值不代表工作偏压下有效值,https://ds.murata.com/simserve/characteristics?ReqType=TechP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
GRM155R71H103KA88D,10nF,1,Murata,MainBoard:C6,原理图已选完整MPN,MLCC标称值不代表工作偏压下有效值,https://ds.murata.com/simserve/characteristics?ReqType=TechP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
GRM188R61A475KE15D,4.7uF,1,Murata,ExtendBoard:C2,原理图已选完整MPN,MLCC标称值不代表工作偏压下有效值,https://ds.murata.com/simserve/characteristics?ReqType=TechP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
GRM188R71E105KA12D,1uF,2,Murata,"MainBoard:C24, ExtendBoard:C4",原理图已选完整MPN,25V/1uF/X7R±10%/0603；与ExtendBoard:C4同料C86020，各焊1颗；BH1750 DVI保留R11=1k，冷启动/快速重启时序须实测; 25V/1uF/X7R±10%/0603；5V本地旁路，与MainBoard:C24同料C86020，各焊1颗；供电与热插拔须实测,https://ds.murata.com/simserve/characteristics?ReqType=TechP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
GRM21BR61E226ME44L,22uF,4,Murata,"MainBoard:C2, MainBoard:C3, MainBoard:C4, MainBoard:C13",原理图已选完整MPN,22uF/25V0805；3V3典型有效约13–15uF，非保证下限; 22uF/25V0805；5V典型有效约10–11uF，非保证下限,https://ds.murata.com/simserve/characteristics?ReqType=TechP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
MMBT3904-7-F,MMBT3904-7-F,2,Diodes Incorporated,"MainBoard:VT1, MainBoard:VT2",厂家图纸已核,B1/E2/C3；按Diodes受控SOT23焊盘，不任意替换不同引脚8050,https://www.diodes.com/assets/Datasheets/MMBT3904.pdf
MPU-6050,MPU6050,1,TDK InvenSense,MainBoard:U3,Obsolete（原厂）,仅可追溯旧库存复刻；需来料功能检验；非持续量产供货方案,https://product.tdk.com/en/search/sensor/mortion-inertial/im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
P133H002,P133H002,1,POLCD,ExtendBoard:LCD1,电气候选，机械待验收,12pin/0.7mm/ST7789V；5.5x0.5mm无F.Paste长焊盘，PCBA后手工焊FPC；仅核纵向落点，折弯/接触面/整壳仍待样件,https://www.polcd-digital.com/products/1-3-inch-tft-lcd-disp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
RC0402FR-07100KL,100k,3,YAGEO,"MainBoard:R18, MainBoard:R19, ExtendBoard:R3",未单独核验生命周期,,https://www.yageogroup.com/component-documentation/download/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
RC0402FR-0710KL,10K / 10k,8,YAGEO,"MainBoard:R1, MainBoard:R6, MainBoard:R7, MainBoard:R8, MainBoard:R9, MainBoard:R10, MainBoard:R16, MainBoard:R17",未单独核验生命周期,,https://www.yageogroup.com/component-documentation/download/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
RC0402FR-0712KL,12K,2,YAGEO,"MainBoard:R4, MainBoard:R5",未单独核验生命周期,,https://www.yageogroup.com/component-documentation/download/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
RC0402FR-071KL,1k,2,YAGEO,"MainBoard:R11, ExtendBoard:R1",未单独核验生命周期,,https://www.yageogroup.com/component-documentation/download/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
RC0402FR-0733RL,33,1,YAGEO,MainBoard:R20,未单独核验生命周期,,https://www.yageogroup.com/component-documentation/download/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
RC0402FR-074K7L,4.7k,2,YAGEO,"MainBoard:R14, MainBoard:R15",未单独核验生命周期,,https://www.yageogroup.com/component-documentation/download/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
RC0402FR-075K1L,5.1k,2,YAGEO,"MainBoard:R12, MainBoard:R13",未单独核验生命周期,,https://www.yageogroup.com/component-documentation/download/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
RC0402JR-070RL,0,1,YAGEO,MainBoard:R2,未单独核验生命周期,0ohm0402，型号额定1A；3V3A支路按ESP≤500mA设计分配,https://www.yageogroup.com/component-documentation/download/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
RC0603FR-0727RL,27,1,YAGEO,ExtendBoard:R2,未单独核验生命周期,,https://www.yageogroup.com/component-documentation/download/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
RTT022000FTH,200R,1,RALEC,MainBoard:R3,原厂规格已核,UART串联200ohm±1%/0402；原位兼容；现有密集land与原厂推荐图有差异，落锡/贴装工艺须验收,https://www.ralec.com/upload/media/product/file/IE-SP-010%20.pdf
SN74AHCT1G125DCKR,SN74AHCT1G125DCKR,1,Texas Instruments,MainBoard:U8,Active（原厂）,保持完整封装后缀与引脚定义,https://www.ti.com/product/SN74AHCT1G125
TPD1E10B06DPYR,TPD1E10B06DPYR,1,Texas Instruments,MainBoard:D2,Active（原厂）,保持完整封装后缀与引脚定义,https://www.ti.com/product/TPD1E10B06
TPD4E05U06DQAR,TPD4E05U06DQAR,1,Texas Instruments,MainBoard:U7,Active（原厂）,保持完整封装后缀与引脚定义,https://www.ti.com/product/TPD4E05U06
TPS22918DBVT,TPS22918DBVT,1,Texas Instruments,MainBoard:U6,Active（原厂）,同TPS22918芯片及DBV6脚；T为250pcs小盘，ON/CT网络不变；2026-10-30嘉立创需订货（渠道快照，库存/交期下单复核）,https://www.ti.com/product/TPS22918
TPS62162DSGR,TPS62162DSGR,1,Texas Instruments,MainBoard:U2,Active（原厂）,保持完整封装后缀与引脚定义,https://www.ti.com/product/TPS62162
USB4105-GF-A,USB4105-GF-A,1,GCT,MainBoard:USB1,厂家图纸已核,按GF-A后缀和B4图采购；需USB数据、热插拔及壳口样件验收,https://gct.co/connector/usb4105
VLS3012HBX-2R2M-N,2.2uH,1,TDK,MainBoard:L1,未单独核验生命周期,2.2uH；完整HBX/-N订货号，电感饱和及温升按供电实测验收,
WS2812B-V5/W,WS2812B-V5/W,1,Worldsemi,MainBoard:D1,厂家资料已核,完整V5/W版本；1VDD/2DOUT/3GND/4DIN；5V供电及AHCT缓冲,https://datasheet.lcsc.com/lcsc/2206131216_Worldsemi-WS2812B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
